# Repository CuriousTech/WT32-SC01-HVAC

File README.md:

# WT32-SC01-HVAC  

WiFi Smart Omniscient Opensource Arduino ESP32 HVAC Touchscreen Thermostat using WT32-SC01 (not PLUS)  OSHPark [Rev1](https://oshpark.com/shared_projects/ljZTJh9A) $15.65  [Rev2](https://oshpark.com/shared_projects/giHlVB41)  

This code is currently too large for ESP-IDF 3.x.x but may be optimized further at some point. Another option is to replace the ESP32-WROVER-B module with the newer WROVER-E-N8R8 or N16R8, which increases the code space by 2x or even 4x.
  
This is the 3rd thermostat I've designed, only because new hardware makes it better, and tends to remove some limitations.  
All sensors from [ESP-HVAC](https://github.com/CuriousTech/ESP-HVAC), and older models can be used as remote units by building as REMOTE. This model can be changed to remote with just a temp/humidity sensor on the i2c pins, plus speaker if desired, and use the USB for power.  
  
This first version just emulated the Nextion HMI and kept all the code the same, except for Display.cpp/h, removal of any ESP8266 specific code, and the addition of an I/O pin to power the H/T sensor for reset purposes since it shares the i2c with the touch interface.  
Encoder.cpp/h was removed, but can be added back easily, with 4 extra I/O pins for expansion (IO36 is input only).  

The WT32-SC01 can be purchased from many vendors. It stays fairly cool, but the LM1117 is a bit inefficient, with a quiescent current of 5mA. These 2 linear regulators can be replaced with something better such as the AP2111H-3.3TRG1 to run it cooler. Soldering iron may be safer than a hot air gun unless the display is pulled away from the PCB (easy).  
  
To program: Copy the User_Setup/Setup201_WT32_SC01.h over the original. Some parameters were incorrect.  
Uncomment #include "Setup201_WT32_SC01.h" and comment the default in TFT_eSPI/User_Setup_Select.h  
Flash over USB first, and upload the SPIFFS data using ESP32 Sketch Data Uploader.  
If any libraries are missing, the error should be on the line with a link to the library. Some are in my ESP-HVAC repo.  
  
Some lines in code to change:  
&nbsp;&nbsp;&nbsp;&nbsp; Thermostat.ino: Uncomment the temp sensor used.  
&nbsp;&nbsp;&nbsp;&nbsp; HVAC.h: Uncomment #define REMOTE to compile for remote units. RMT1 should be changed to a uniique ID for each remote.  
&nbsp;&nbsp;&nbsp;&nbsp; WebHandler.cpp: ipFcServer(192,168,31,100); is the local forecast server IP. This is a comma delimited file for the current temps on a local server.  
&nbsp;&nbsp;&nbsp;&nbsp; eeMem.h: This has the SSID/password (or use EspTouch to set up), web access password, and OpenWeatherMap city ID, and many other default EEPROM values.  
&nbsp;&nbsp;&nbsp;&nbsp; OpenWeaetherMap.h: #define APPID "app id" is the long string from OpenWeatherMap.  
  
First test of the board came out almost perfect. The via close to the rectangle speaker can touch metal on the speaker and short. Use capton tape. It can go on the bottom or top. Bottom is better. The right capacitor doesn't clear the ESP32, even at 7mm tall. It only needs about 100uF at 25V, but more is better. They can be mounted to the back with the current case design.  
  
Thermal issues have been a struggle with this design, and the SHT40 is horrible sharing the i2c bus with the touchscreen. The AM2322 or AM2320 is a much better option. To reduce current, which effectively reduces heat, several changes were made: Setting clock to 80MHz instead of the default 240MHz, disabling the bluetooth radio, and lowering the LED backlight brightness (100 of 255) drops it from ~250mA to 150mA at 5V. Reducing the brightness further to 50 brings it down to ~80mA. At this point it produces very little heat, and is still almost bright enough for indoor visibility. 100 is really preferable.  

With the printed case. I added about 5 inches of black before the white to match the display face (just stuck in front, not fused).  

HVAC wiring labels:  
 C (blue) common 24VAC  
 Rc (red or orange) 24VAC power for cool  (C and Rc power the thermostat)  
 Rh (red) 24VAC power for heat. Solder the Rc-Rh jumper on the back if not used.  
 Y (yellow) cool signal  
 O (color varies) compressor reverse for heatpump  
 W (white) heat signal  
 G (green) fan signal. Note: Heat and cool override manual fan signal.  
 H humidifier  
  
Main page:  

Cool/heat low/high:  
These are the desired temperature ranges for cooling and heating, which are calculated based on outside temperature over the next set number of days if using forecast.  

Cycle:  Disable heat and cool, but still cycles the fan by the Auto Fan: Run: settings. 4:00 and 5 default = 5 minutes every 4 hours.  

Threshold:  
The temperature offset to complete a cycle.  

Pre-cycle fan time:  
0 disables, 1 second to 5 minutes.  This is the first phase of the cycle.  When the temperature reaches the target, the fan is turned on to cycle air for the set time, which causes the thermostat to read a more overall temperature. If the threshold is reached before this ends, which it can, it will shut off. Otherwise it continues to the run phase, which runs for at least the cycleMin period to save wear on the compressor because this does shorten the run time considerably.  A good value to use is the time it takes to lower the temperature after turning the fan on before it plateaus.  Usually around 2 minutes. Note: The compressor and furnace have built-in timers as well, so make sure it's above them or it can get out of sync.  

Post-cycle fan time:  
Runs fan after cycle completes. This is the third phase of the cycle, which continues to push air through the cold radiator and ductwork. 2 minutes is good, but you can use an IR thermometer on a vent to see how long the cold air continues.  

Humidifier settings:  
Off: Always off  
Fan: Run when fan is on  
Run: Run when thermostat is running a cycle  
Auto1: Operate by humidistat during run cycles  
Auto2: Humidistat runs independently of thermostat (shares fan control)  

Override:  
Use to heat or cool by a selected offset temperature for a specified time.  

Freshen:  
Starts the fan with a timeout.  This uses the post fan timer, so a normal cycle will cancel it.  

Idle min, cycle min/max:  
These are timers in seconds to control the thermostat operating limits.  Idle min is the shortest time between cycles.  Cycle min is the shortest time for a cycle, and max is the longest.  The compressor has its own timers, so too short can get out of sync with the operation.  

Away time and temperature delta offset:  
The away time is in hours:minutes unlike the rest of the timers, but uses the override timer.  It can be turned on and off with the button, but will also turn off with the timer.  There are 2 temp values that are displayed depending on heat or cool mode.  One for heat and one for cool, like the pre/post fan.
Like any setting, it can be automated with something like Tasker.  To turn on would be <b>http://ip/s?key=password&away=1</b>  

Other settings:  
AC differential limit: Increases thermostat if inside/outside difference is more than 20. This assumes Fahrenheit. Change for Celsius.  
Heat Threshold: Heatpump will switch off and use gas when outside temp goes below set value (default 33). Change for Celsius.  
PKW (price per kilowatt hour), CFM (gas cubic feet per minute), CCF (cost per 100 cubic foot): Set the PPKW and CCF based on billing. CFM is dependent on the furnace.  
FC Shift (in minutes): Shifts the forecast for the temperature adjust. Use the setting on the chart page (they don't affect the actual settings) to determine what's best. There are 2 values for heat and cool here as well.   
Lookahead is for the forecast data. 23*3 hours default is a good range to find peaks in the current forecast. Disp is the amount to display on the unit.  
Brightness is the dim and bright backlight levels.  
Cal is calibration of the temp sensor.  
The arrows control the weight averaging of the internal temp sensor and remote sensors. Set them higher in rooms you're more often using or occupancy sensors can bump the weight.  

The web chart.  Dark gray is off, cyan is fan running, blue is compressor+fan, NG is red, HP is yellow, rh is green, the target/threshold is the wave.  The thermostat is in the hottest room in the house, so it does look warmer than it really is, but that's why there's a remote unit, and now multiple sensors.  

Sensor web page

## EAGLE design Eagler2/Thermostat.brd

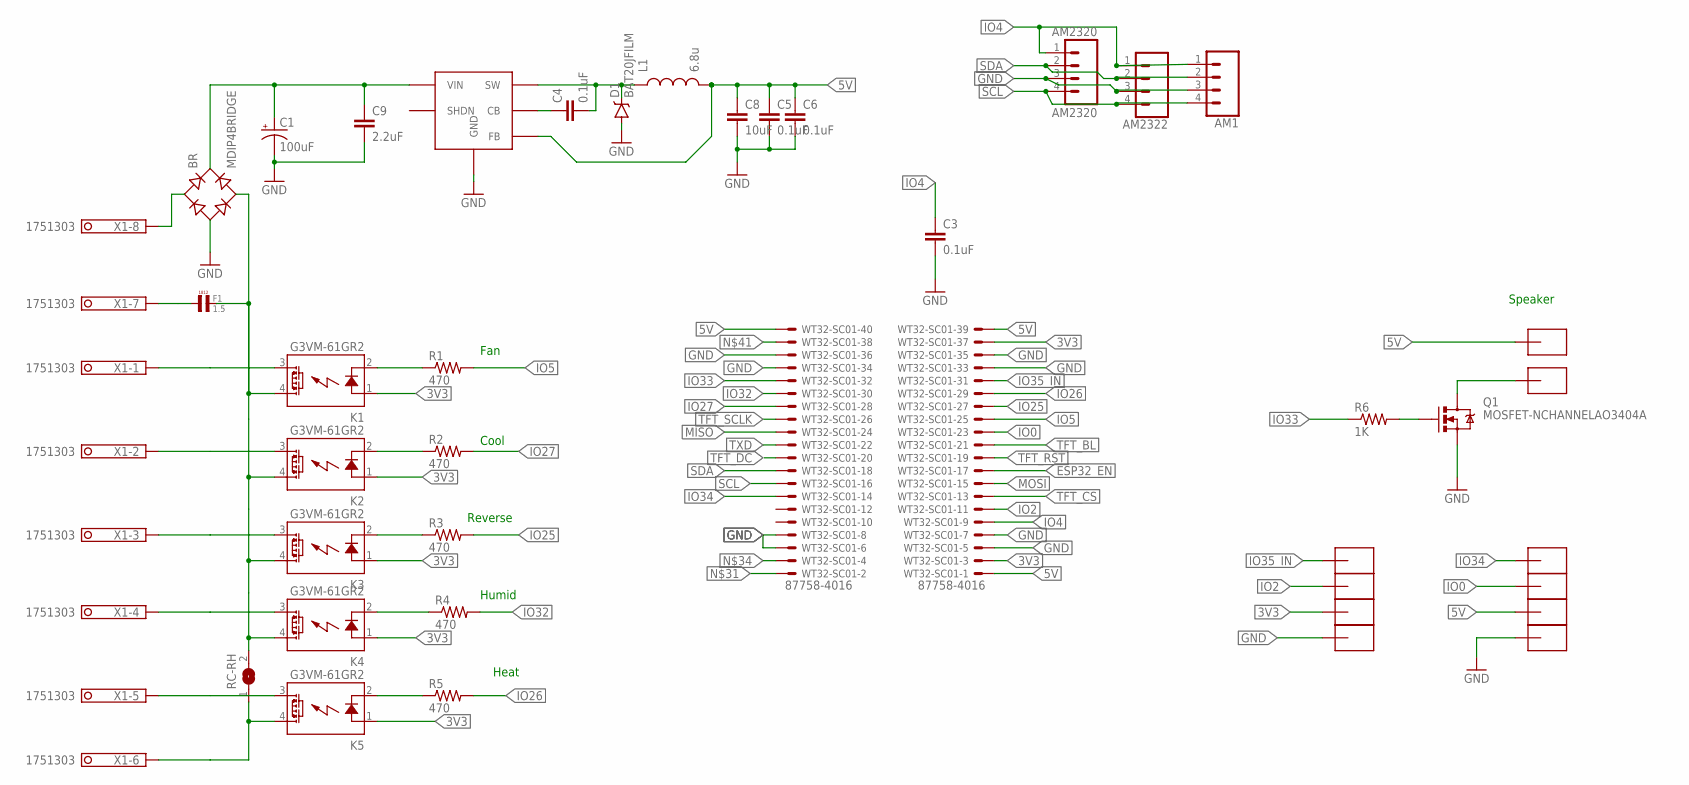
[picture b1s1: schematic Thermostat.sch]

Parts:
AM1, AM2322: CONN_041.27MM; 1X04_1.27MM
AM2320: AM2320; 1X04
BR: MDIP4BRIDGE; MICRODIP4
C1: 100uF; PANASONIC_C
C3, C4, C5, C6: 0.1uF; 0805
C8: 10uF; 0805
C9: 2.2uF; 0805
D1: BAT20JFILM; SOD-323
F1: 1.5; L4,8
K1, K2, K3, K4, K5: G3VM-61GR2; SOP04
L1: 6.8u; 1007
Q1: MOSFET-NCHANNELAO3404A; SOT23-3
R1, R2, R3, R4, R5: 470; 0805
R6: 1K; 0805
RC-RH: SJ
U$1, U$2, U$3, U$4, U$5, U$6, U$7, U$9, U$10, U$11: SMD-PAD1SMD-PAD80X32; SMD-PAD6
VREG: LMR16006YQ; SOT-23-6
WT32-SC01: 87758-4016
X1: 1751303

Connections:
3V3: K1.1 (A), K2.1 (A), K3.1 (A), K4.1 (A), K5.1 (A), U$1.>PAD, WT32-SC01.3, WT32-SC01.37
5V: C5.1, C6.1, C8.1, L1.2, U$5.>PAD, U$7.>PAD, VREG.3 (FB), WT32-SC01.1, WT32-SC01.39, WT32-SC01.40
ESP32_EN: WT32-SC01.17
GND: AM1.3, AM2320.3, AM2322.3, BR.-, C1.-, C3.2, C5.2, C6.2, C8.2, C9.2, D1.A, Q1.2 (S), U$2.>PAD, U$9.>PAD, VREG.2 (GND), WT32-SC01.5, WT32-SC01.6, WT32-SC01.7, WT32-SC01.8, WT32-SC01.33, WT32-SC01.34, WT32-SC01.35, WT32-SC01.36
IO0: U$10.>PAD, WT32-SC01.23
IO2: U$3.>PAD, WT32-SC01.11
IO4: AM1.1, AM2320.1, AM2322.1, C3.1, WT32-SC01.9
IO5: R1.2, WT32-SC01.25
IO25: R3.2, WT32-SC01.27
IO26: R5.2, WT32-SC01.29
IO27: R2.2, WT32-SC01.28
IO32: R4.2, WT32-SC01.30
IO33: R6.1, WT32-SC01.32
IO34: U$6.>PAD, WT32-SC01.14
IO35_IN: U$4.>PAD, WT32-SC01.31
MISO: WT32-SC01.24
MOSI: WT32-SC01.15
unnamed: C4.2, D1.C, L1.1, VREG.6 (SW)
unnamed: BR.AC2, F1.P$2 (2), K1.4 (DS1), K2.4 (DS1), K3.4 (DS1), K4.4 (DS1), RC-RH.2
unnamed: K4.2 (K), R4.1
unnamed: Q1.1 (G), R6.2
unnamed: K3.2 (K), R3.1
unnamed: K2.2 (K), R2.1
unnamed: K4.3 (DS2), X1.4
unnamed: K2.3 (DS2), X1.2
unnamed: K1.3 (DS2), X1.1
unnamed: K1.2 (K), R1.1
unnamed: C4.1, VREG.1 (CB)
unnamed: K5.3 (DS2), X1.5
unnamed: BR.AC1, X1.8
unnamed: K5.4 (DS1), RC-RH.1, X1.6
unnamed: F1.P$1 (1), X1.7
unnamed: BR.+, C1.+, C9.1, VREG.5 (VIN)
unnamed: K5.2 (K), R5.1
unnamed: K3.3 (DS2), X1.3
unnamed: Q1.3 (D), U$11.>PAD
SCL: AM1.4, AM2320.4, AM2322.4, WT32-SC01.16
SDA: AM1.2, AM2320.2, AM2322.2, WT32-SC01.18
TFT_BL: WT32-SC01.21
TFT_CS: WT32-SC01.13
TFT_DC: WT32-SC01.20
TFT_RST: WT32-SC01.19
TFT_SCLK: WT32-SC01.26
TXD: WT32-SC01.22

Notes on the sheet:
Speaker
Fan
Cool
Reverse
Humid
Heat

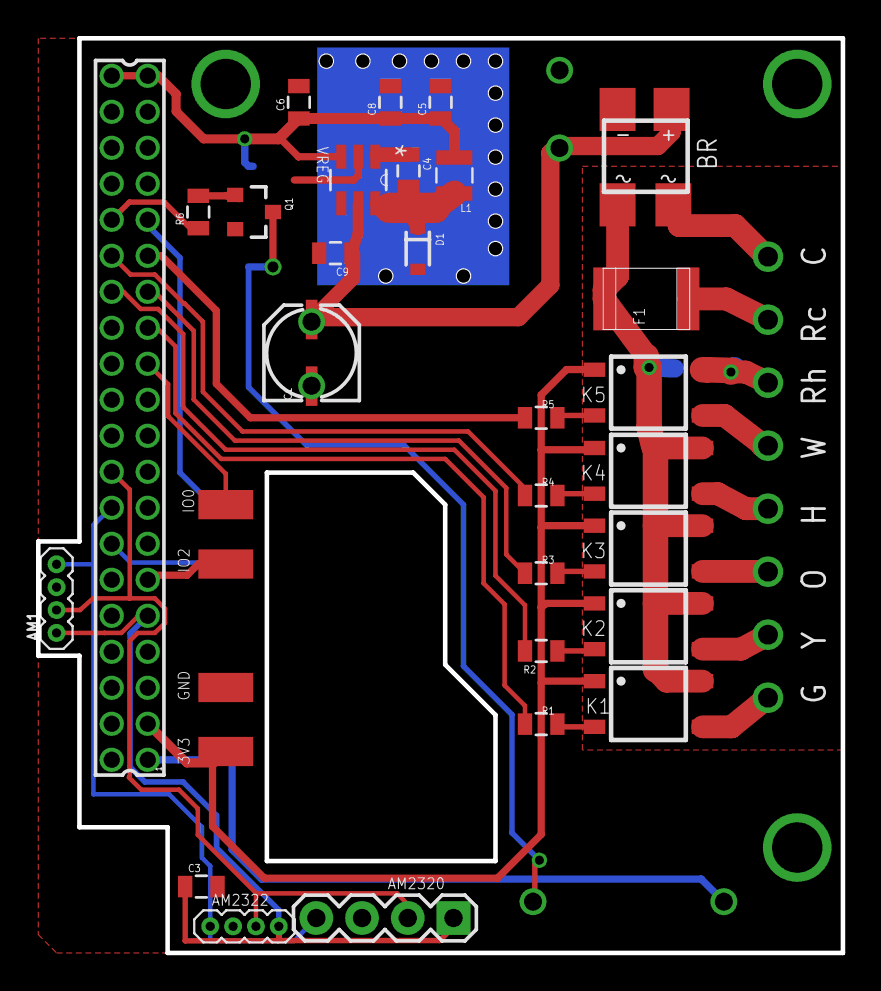
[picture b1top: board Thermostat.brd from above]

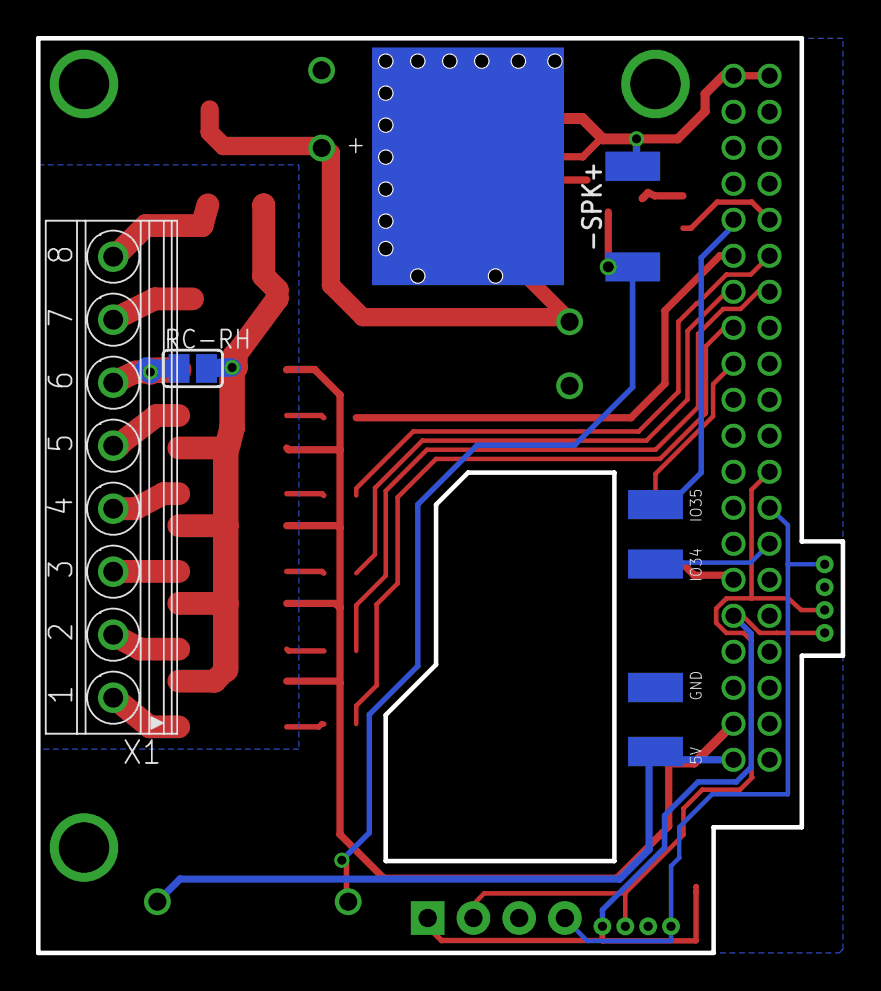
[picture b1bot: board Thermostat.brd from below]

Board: 2 copper layers, 44.7 x 50.8 mm, 40 parts (8 on the bottom side), 35 nets.

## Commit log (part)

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2023-10-18 Update Thermostat.ino
    Sensor reset
2023-10-21 Updated chart graphics
2023-10-24 Added humidifier buttons
2023-10-24 More precision in outdoor temp
2023-10-24 Delete Arduino/pages.h
    Not used anymore
2023-10-24 Openweathermap now has more precision
2023-10-24 Future weather info storage
2023-10-24 Added humidity and 0.1 temp res
2023-10-24 Removed non-SPIFFS pages, changed forecast struct
2023-10-24 Added humidifier functions
2023-10-24 Added a button
2023-10-24 Moved screensavers, added humidifier button
2023-10-31 Cleaning up a bit
2023-10-31 Moved analog clock to screensavers
2023-11-04 Removed Wire.begin()
2023-11-04 Removed a console.log
2023-11-04 Clearer connector options
2023-11-04 Still working on this
2023-11-04 Modified SHT40 code
2023-11-04 Many changes for new UI
2023-11-04 Added larger fonts
2023-11-04 Use of shared buffer for efficiency
2023-11-04 A little tidy-up
2023-11-06 Working on new UI
2023-11-07 Moved adjust link to display
2023-11-07 Removed 14pt font
2023-11-08 UI changes
2023-11-08 Added lock, moved digits around
2023-11-08 Humidifier adjust response
2023-11-11 Moved more active data out
2023-11-11 update() checks for change
2023-11-11 daily/monthly stats moved
2023-11-11 stats moved
2023-11-13 Possibly made some slight changes
2023-11-13 Added backlight level command
2023-11-13 Lowered BL brightness
2023-11-13 Shut down BT, changed to ESP32 Dev Module
2023-11-18 Changed forecast struct
2023-11-18 Added weather ID
2023-11-18 Added weather icons
2023-11-19 Better for the icons
2023-11-19 typo
2023-11-19 Shifted weather icons down
2023-11-23 Moved code
2023-11-23 Merged OpenWeatherMap
2023-11-23 Merged OWM and forecast display
2023-11-23 Moved forecast display to other file
2023-11-23 Forecast ref changes
2023-11-26 Left hard coded IP in
2023-11-26 Weather icon added to clock
2023-11-26 Added drawIcon for clock
2023-11-26 added drawIcon, a few fixes
2023-11-30 Display corrections
2023-11-30 Backlight changes
2023-11-30 Backlight, notification changes
2023-11-30 Humidifier remote changes
2023-11-30 Added 1 note
2023-11-30 Cleaned up a bit
2023-12-04 Lowered idle brightness more
2023-12-04 Removed log in remote
2023-12-04 Moved hostname here
2023-12-04 Switched to esp WebSocket client for stability
2023-12-04 Display fix
2023-12-04 Saving space
2023-12-08 Touch brighten works better
2023-12-08 better hvac found/not found notifs, removed input on some uris
2023-12-08 small bugfix
2023-12-10 Aligned digits
2023-12-10 OTA Update notification
2023-12-10 Shows remote temp when RH is tapped (temporary)
2023-12-10 Shifted temp/rh a bit
2023-12-10 Added more notifs
2023-12-10 Removed SHT40 code
2023-12-10 Removed SHT40
2024-01-20 Changed legend buttons
2024-01-20 brightness var changed
2024-01-20 Fixed dec place of outmin/max, furnace blower timer halved for 1/2 power
2024-01-30 The MIC was wrong 3V3 linear for this
2024-02-09 New buttons for main screen
2024-02-09 Added brightness settings
2024-02-09 forecast/history now called from buttons
2024-02-09 Untested heat/cool fail warnings, brightness settings
2024-02-09 Added forecast display when updates occur
2024-02-22 Same as r0/r1 but optional side sensor for tabletop, 1st cap on back next to bridge rect.
2024-03-08 For rev2 board with side sensor (freestanding)
2024-05-02 Updated SSR resistors
2025-03-10 Add link to file manager
2025-03-10 Optimizing mostly
2025-03-10 Override button added
2025-03-10 Override and fileman stuff
2025-03-10 A lot of cleanup, smaller WS client
2025-03-10 Cut down fonts
2025-03-10 Moved EEPROM to FS
2025-03-10 Allows use of json parser externally
2025-03-10 Commented out unused songs
2025-04-07 shift out only 2 entries each time
2025-04-13 Added history navigation buttons
2025-04-13 Fix not HP heating notif, add usage history files
2025-04-13 Add HP not heating notif
2025-04-13 add history filename load
2025-04-13 change eemem file to settings
2025-04-13 Forgot to add this file
2025-04-14 Fix for default stats
2025-04-14 Clear month on 1st day
2025-04-19 Migrating instructions to this repo
2025-04-29 Incorrect history save name
2025-04-29 Alignment of some cells
2025-04-29 Better arrows
2025-04-29 Added restart button
2025-04-29 Missed a change
2025-04-29 IP force commented out again
2025-05-05 Swapped load order for faster manual nav
2025-05-05 Bugfix for buffer pointer after delete
2025-06-04 Fan state color update
2025-06-04 Current day lines removed on older months
2025-06-07 A line was deleted at some point
2025-07-12 Added calendar SS
2025-07-12 found changes in filemanager
2025-07-12 Removed old eemem.bin
2025-07-12 Forced IP wasn't supposed to be there
2025-07-12 False sensor error on startup
2025-07-12 Current day/month number highlight
2025-07-19 Changed to esp32 time functions
2025-07-19 3.x.x compat
2025-07-21 Reducing code space
2025-08-03 Uses long name
2025-08-03 Removed analog clock
2025-08-03 Using long names for sensors
2025-08-03 commented out analog clock
2025-09-07 Added DST
2025-09-07 Cleanup
2025-09-07 Using timezone env
2025-09-07 Time code changes
2025-09-07 Switched to global time var
2025-09-07 Removed DST
2025-09-07 Changed for latest PNGdec
2025-09-07 Global time var, better wifi reconnect
2025-09-07 Global time var
2026-03-30 Changing to JPEG for reduced code size
2026-03-30 Removed debug
2026-03-30 Replaced digital font with drawing
2026-03-30 Added call to a wifi damper
2026-03-30 Changed from PNG to JPG loader
2026-03-30 added setDamper function
2026-03-30 added damper IP
2026-03-30 added generic local call
2026-03-30 Updated to state that it works with IDF 3.3.7
2026-04-14 Signed offset fix
2026-04-17 Forgot one
2026-04-17 Simpler tz set
2026-04-17 Fix what I broke last time
2026-04-17 Added the root / back in
2026-04-25 Update: Use ESP32 WRover Module
2026-04-25 Refactor Display.h to remove redundant code
2026-04-25 Removed dimming, added gfx buffering
2026-04-25 push image to sprite
2026-04-25 A little cleanup
2026-04-25 Switched to sprite output
2026-04-25 Add sprite support to screensavers header
2026-04-25 Update README with hardware upgrade option
    Added information about code size limitations and hardware options.
2026-04-26 Missed a refresh skip
2026-05-03 AM2320 integer value return
2026-05-03 AM2320 integer value return
    Added AM2320 sensor library for temperature and humidity measurement.
2026-05-03 Refactor sensor measurement to use integers
2026-05-03 Refactor temperature handling to use int16_t
2026-05-03 Added restart code, removed static fm.html
2026-05-03 Added restart code
2026-05-03 add shutdown method
2026-05-03 Added degree symbol
2026-05-03 Adjusts for degree symbol
2026-05-03 Refactor Media.cpp for clarity and efficiency
    Removed unnecessary lines and simplified the tft_output function. Updated loadImage method to directly construct the image path.
2026-05-03 Removed offset loadimage
2026-05-03 Cleanup for new drawfakefloat
2026-05-03 Added stop function
2026-05-03 Add stop method to Music class
    Added a stop method to the Music class.
2026-05-04 Update README with image and project details
    Added image and improved project description.
2026-05-22 Changed ip to name in custom connect
2026-05-22 Reworked wifi connection handler
2026-06-01 Changed websocket for proxy
2026-06-01 Refactor WebSocket connection and improve path handling
    Updated WebSocket connection handling and added relative path support.
2026-06-01 Refactor WebSocket connection and file upload handling
2026-06-01 Refactor WebSocket connection
    Updated WebSocket connection handling and added relative path support for WebSocket URL.
2026-06-01 Removed the /iot to / access, websocket reconnect on loss
2026-06-14 Reduce damper calls
2026-06-14 Avoid forecast timer reset on damper calls
2026-06-20 Refactor BasicSensor.cpp and add setDST method
    Refactor variable declarations and add setDST method.
2026-06-20 Add setDST
2026-06-20 Removed tz
    Updated eeMem structure by modifying variable names and types, adjusting sizes, and changing default values.
2026-06-20 Remove TZ input
    Removed timezone input field from the UI and adjusted related HTML.
2026-06-20 Update Tuya interface with temperature and humidity handling
2026-06-20 Refactor TuyaInterface class member declarations
2026-06-20 Adjust time calculations

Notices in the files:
parts and their libraries:
SparkFun-Connectors: Licensing: CC v3.0 Share-Alike You are welcome to use this library for commercial purposes.
SparkFun-Resistors: Licensing: Creative Commons ShareAlike 4.0 International - https://creativecommons.org/licenses/by-sa/4.0
